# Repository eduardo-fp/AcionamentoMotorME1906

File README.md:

# 🚀 Arduino Full-Bridge Shield: Acionamento de Potência para Motor ME19006 (ME0909)

O objetivo principal é criar uma ponte completa (*Full-Bridge*) robusta e didática para realizar ensaios de eficiência e testes de técnicas avançadas de modulação chaveada no motor **ME19006 (ME0909)**, utilizado no barco da equipe de corrida **Zênite Solar (IFSC)**.

A arquitetura foi pensada em formato Shield para o ecossistema Arduino, facilitando a troca rápida de códigos de controle e aquisição de dados durante as bancadas de teste.

## 📋 Especificações do Sistema

O projeto foi dimensionado para operar nas condições reais de teste da equipe de barco solar, trabalhando com alta margem de segurança elétrica e térmica:

| **Parâmetro / Componente** | **Especificação** | **Descrição / Justificativa** |
| :--- | :--- | :--- |
| **Tensão de Barramento** | `60V DC` | Tensão nominal de alimentação do barramento de tração do barco da equipe **Zênite Solar (IFSC)**. |
| **Corrente Máxima** | `50A` | Corrente máxima de teste estipulada para validação das modulações do TCC. |
| **Motor Alvo** | `ME19006 (ME0909)` | Motor utilizado no barco da equipe Zenite Solar (IFSC). |
| **Gate Driver** | `MP1923` | Driver Half-Bridge de 100V. Fornece 7A/8A de pico. |
| **MOSFET de Potência** | `IXFN420N10T` | MOSFET utilizado no barco da equipe Zenite Solar(IFSC). |
| **Frequência de Chaveamento** | `6 kHz a 12 kHz` | Faixa de frequência de modulação otimizada para o motor e para minimizar perdas no driver. |

## 🛡️ Destaques de Projeto da PCB

Para garantir que a placa funcione de forma estável sob correntes de 50A e barramento de 60V, as seguintes proteções e metodologias foram implementadas no layout:

1. **Rede de Bootstrap Otimizada:** Dimensionada utilizando o pior caso de chaveamento (**6 kHz**). Capacitores cerâmicos SMD de **4.7 µF (50V X7R)** foram selecionados para compensar as correntes quiescentes do driver e a perda de capacitância por efeito de *DC Bias*.

2. **Filtros Snubber RC:** Integrados fisicamente rentes aos drenos e fontes dos MOSFETs IXFN420N10T para mitigar os picos de sobretensão causados pela indutância parasita das trilhas na comutação.

3. **Dimensionamento de Trilhas de Potência:** Áreas de cobre superdimensionadas e estanhadas para suportar a densidade de corrente de 50A sem elevação excessiva de temperatura (calculado via IPC-2152).

## 📂 Estrutura do Repositório

O repositório está organizado para facilitar a replicação, fabricação e auditoria do projeto:

```text
📦 AcionamentoMotorME1906
 ┣ 📂 Hardware
 ┃ ┣ 📜 Esquemático (Arquivos fontes e PDF)
 ┃ ┣ 📜 PCB Layout (Arquivos de design e Gerbers para fabricação)
 ┃ ┣ 📜 BOM_Custos.csv (Lista de Materials e Orçamento do Projeto)
 ┃ ┗ 📜 Modelos 3D (Arquivos STEP para integração mecânica do Shield)
 ┣ 📂 Docs
 ┃ ┣ 📜 Calculos (Bootstrap, Snubber e dimensionamento de trilhas)
 ┃ ┗ 📜 Datasheets (Documentações técnicas do MP1923 e IXFN420N10T)
 ┣ 📂 Software
 ┃ ┗ 📜 Codigos Arduino (Implementação das rotinas de controle e PWM)
 ┗ 📜 README.md

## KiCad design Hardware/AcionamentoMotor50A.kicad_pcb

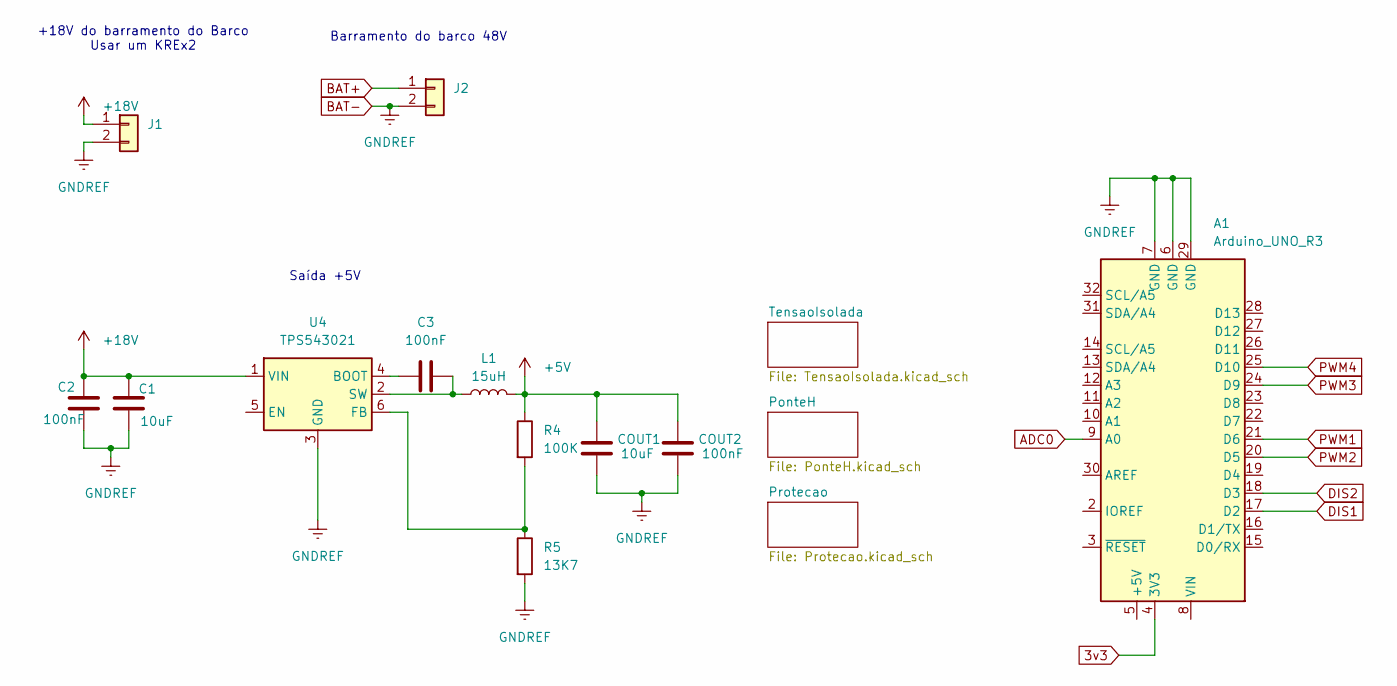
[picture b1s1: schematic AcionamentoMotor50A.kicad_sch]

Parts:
A1: Arduino_UNO_R3
C1: 10uF; C_0805_2012Metric_Pad1.18x1.45mm_HandSolder
C2, C3: 100nF; C_0805_2012Metric_Pad1.18x1.45mm_HandSolder
COUT1: 10uF; C_0805_2012Metric_Pad1.18x1.45mm_HandSolder
COUT2: 100nF; C_0805_2012Metric_Pad1.18x1.45mm_HandSolder
J1, J2: Conn_01x02; TerminalBlock_Phoenix_MKDS-1,5-2_1x02_P5.00mm_Horizontal
L1: 15uH; L_0805_2012Metric_Pad1.05x1.20mm_HandSolder
R4: 100K; R_0805_2012Metric_Pad1.20x1.40mm_HandSolder
R5: 13K7; R_0805_2012Metric_Pad1.20x1.40mm_HandSolder
U4: TPS543021; SOT-563

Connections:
3v3: A1.4 (3V3)
5V: COUT1.2, COUT2.2, L1.2, R4.1; also elsewhere on the board
+18V: C1.1, C2.1, J1.1, U4.1 (VIN); also elsewhere on the board
ADC0: A1.9 (A0); also elsewhere on the board
BAT+: J2.1; also elsewhere on the board
BAT-: A1.6 (GND), A1.7 (GND), A1.29 (GND), C1.2, C2.2, COUT1.1, COUT2.1, J1.2, J2.2, R5.2, U4.3 (GND); also elsewhere on the board
DIS1: A1.17 (D2); also elsewhere on the board
DIS2: A1.18 (D3); also elsewhere on the board
unnamed: C3.1, U4.4 (BOOT)
unnamed: R4.2, R5.1, U4.6 (FB)
unnamed: C3.2, L1.1, U4.2 (SW)
PWM1: A1.21 (D6); also elsewhere on the board
PWM2: A1.20 (D5); also elsewhere on the board
PWM3: A1.24 (D9); also elsewhere on the board
PWM4: A1.25 (D10); also elsewhere on the board

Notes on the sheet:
Saída +5V
Barramento do barco 48V
+18V do barramento do Barco Usar um KREx2

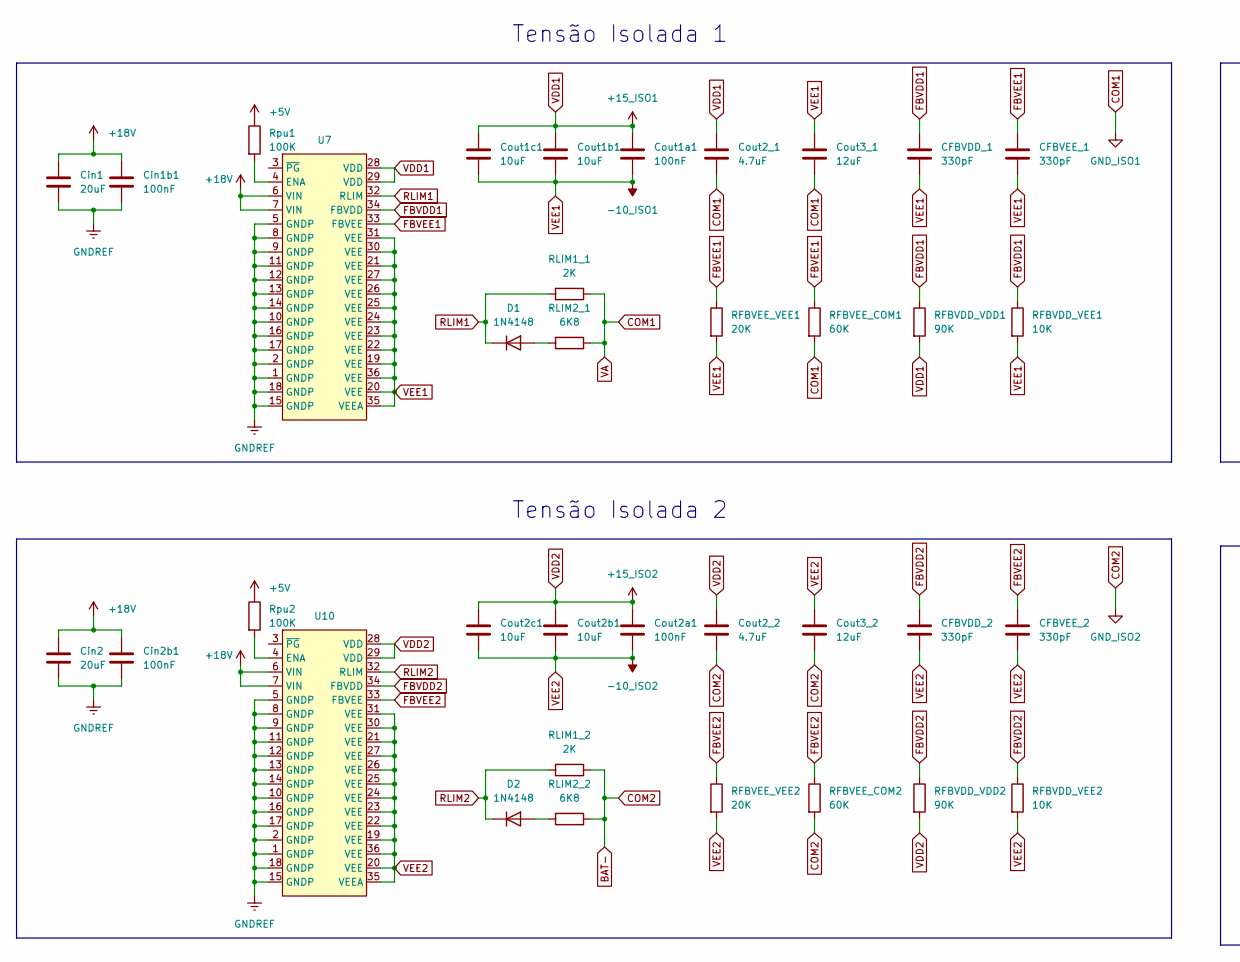
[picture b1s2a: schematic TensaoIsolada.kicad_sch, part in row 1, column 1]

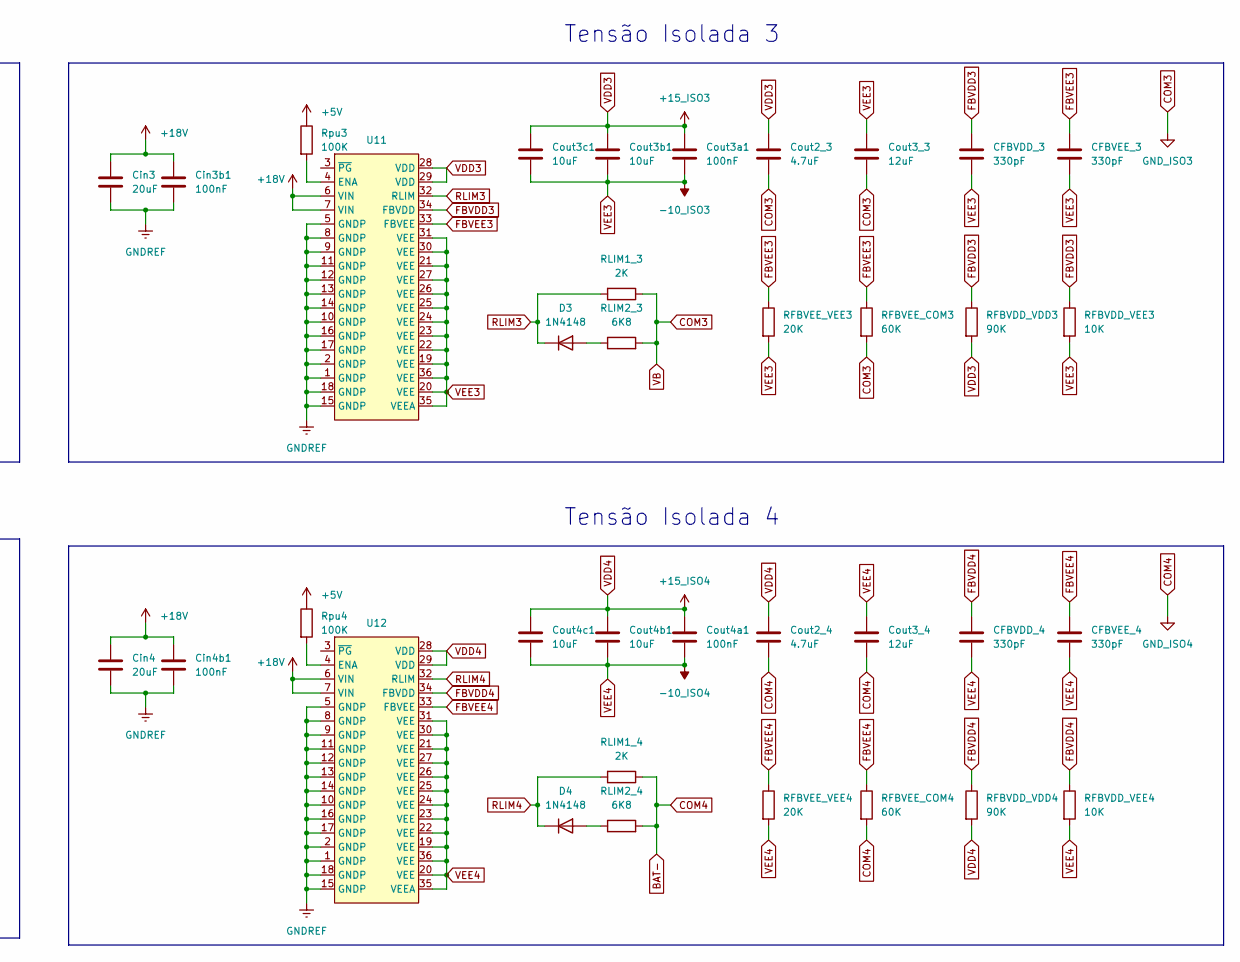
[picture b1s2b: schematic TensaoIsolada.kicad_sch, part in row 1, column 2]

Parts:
CFBVDD_1, CFBVDD_2, CFBVDD_3, CFBVDD_4: 330pF; C_0805_2012Metric_Pad1.18x1.45mm_HandSolder
CFBVEE_1, CFBVEE_2, CFBVEE_3, CFBVEE_4: 330pF; C_0805_2012Metric_Pad1.18x1.45mm_HandSolder
Cin1, Cin2, Cin3, Cin4: 20uF; C_0805_2012Metric_Pad1.18x1.45mm_HandSolder
Cin1b1, Cin2b1, Cin3b1, Cin4b1: 100nF; C_0805_2012Metric_Pad1.18x1.45mm_HandSolder
Cout1a1, Cout2a1, Cout3a1, Cout4a1: 100nF; C_0805_2012Metric_Pad1.18x1.45mm_HandSolder
Cout1b1, Cout1c1, Cout2b1, Cout2c1, Cout3b1, Cout3c1, Cout4b1, Cout4c1: 10uF; C_0805_2012Metric_Pad1.18x1.45mm_HandSolder
Cout2_1, Cout2_2, Cout2_3, Cout2_4: 4.7uF; C_0805_2012Metric_Pad1.18x1.45mm_HandSolder
Cout3_1, Cout3_2, Cout3_3, Cout3_4: 12uF; C_0805_2012Metric_Pad1.18x1.45mm_HandSolder
D1, D2, D3, D4: 1N4148; D_DO-35_SOD27_P7.62mm_Horizontal
RFBVDD_VDD1, RFBVDD_VDD2, RFBVDD_VDD3, RFBVDD_VDD4: 90K; R_0805_2012Metric_Pad1.20x1.40mm_HandSolder
RFBVDD_VEE1, RFBVDD_VEE2, RFBVDD_VEE3, RFBVDD_VEE4: 10K; R_0805_2012Metric_Pad1.20x1.40mm_HandSolder
RFBVEE_COM1, RFBVEE_COM2, RFBVEE_COM3, RFBVEE_COM4: 60K; R_0805_2012Metric_Pad1.20x1.40mm_HandSolder
RFBVEE_VEE1, RFBVEE_VEE2, RFBVEE_VEE3, RFBVEE_VEE4: 20K; R_0805_2012Metric_Pad1.20x1.40mm_HandSolder
RLIM1_1, RLIM1_2, RLIM1_3, RLIM1_4: 2K; R_0805_2012Metric_Pad1.20x1.40mm_HandSolder
RLIM2_1, RLIM2_2, RLIM2_3, RLIM2_4: 6K8; R_0805_2012Metric_Pad1.20x1.40mm_HandSolder
Rpu1, Rpu2, Rpu3, Rpu4: 100K; R_0805_2012Metric_Pad1.20x1.40mm_HandSolder
U7, U10, U11, U12: SSOP-36

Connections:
5V: Rpu1.1, Rpu2.1, Rpu3.1, Rpu4.1; also elsewhere on the board
+18V: Cin1.1, Cin1b1.1, Cin2.1, Cin2b1.1, Cin3.1, Cin3b1.1, Cin4.1, Cin4b1.1, U7.6 (VIN), U7.7 (VIN), U10.6 (VIN), U10.7 (VIN), U11.6 (VIN), U11.7 (VIN), U12.6 (VIN), U12.7 (VIN); also elsewhere on the board
BAT-: Cin1.2, Cin1b1.2, Cin2.2, Cin2b1.2, Cin3.2, Cin3b1.2, Cin4.2, Cin4b1.2, Cout2_2.2, Cout2_4.2, Cout3_2.2, Cout3_4.2, RFBVEE_COM2.2, RFBVEE_COM4.2, RLIM1_2.1, RLIM1_4.1, RLIM2_2.2, RLIM2_4.2, U7.1 (GNDP), U7.2 (GNDP), U7.5 (GNDP), U7.8 (GNDP), U7.9 (GNDP), U7.10 (GNDP), U7.11 (GNDP), U7.12 (GNDP), U7.13 (GNDP), U7.14 (GNDP), U7.15 (GNDP), U7.16 (GNDP), U7.17 (GNDP), U7.18 (GNDP), U10.1 (GNDP), U10.2 (GNDP), U10.5 (GNDP), U10.8 (GNDP), U10.9 (GNDP), U10.10 (GNDP), U10.11 (GNDP), U10.12 (GNDP), U10.13 (GNDP), U10.14 (GNDP), U10.15 (GNDP), U10.16 (GNDP), U10.17 (GNDP), U10.18 (GNDP), U11.1 (GNDP), U11.2 (GNDP), U11.5 (GNDP), U11.8 (GNDP), U11.9 (GNDP), U11.10 (GNDP), U11.11 (GNDP), U11.12 (GNDP), U11.13 (GNDP), U11.14 (GNDP), U11.15 (GNDP), U11.16 (GNDP), U11.17 (GNDP), U11.18 (GNDP), U12.1 (GNDP), U12.2 (GNDP), U12.5 (GNDP), U12.8 (GNDP), U12.9 (GNDP), U12.10 (GNDP), U12.11 (GNDP), U12.12 (GNDP), U12.13 (GNDP), U12.14 (GNDP), U12.15 (GNDP), U12.16 (GNDP), U12.17 (GNDP), U12.18 (GNDP); also elsewhere on the board
COM1: Cout2_1.2, Cout3_1.2, RFBVEE_COM1.2, RLIM1_1.1, RLIM2_1.2; also elsewhere on the board
COM3: Cout2_3.2, Cout3_3.2, RFBVEE_COM3.2, RLIM1_3.1, RLIM2_3.2; also elsewhere on the board
FBVDD1: CFBVDD_1.1, RFBVDD_VDD1.1, RFBVDD_VEE1.1, U7.34 (FBVDD)
FBVDD2: CFBVDD_2.1, RFBVDD_VDD2.1, RFBVDD_VEE2.1, U10.34 (FBVDD)
FBVDD3: CFBVDD_3.1, RFBVDD_VDD3.1, RFBVDD_VEE3.1, U11.34 (FBVDD)
FBVDD4: CFBVDD_4.1, RFBVDD_VDD4.1, RFBVDD_VEE4.1, U12.34 (FBVDD)
FBVEE1: CFBVEE_1.1, RFBVEE_COM1.1, RFBVEE_VEE1.1, U7.33 (FBVEE)
FBVEE2: CFBVEE_2.1, RFBVEE_COM2.1, RFBVEE_VEE2.1, U10.33 (FBVEE)
FBVEE3: CFBVEE_3.1, RFBVEE_COM3.1, RFBVEE_VEE3.1, U11.33 (FBVEE)
FBVEE4: CFBVEE_4.1, RFBVEE_COM4.1, RFBVEE_VEE4.1, U12.33 (FBVEE)
unnamed: D1.2 (A), RLIM2_1.1
unnamed: D2.2 (A), RLIM2_2.1
unnamed: D3.2 (A), RLIM2_3.1
unnamed: D4.2 (A), RLIM2_4.1
unnamed: Rpu1.2, U7.4 (ENA)
unnamed: Rpu2.2, U10.4 (ENA)
unnamed: Rpu3.2, U11.4 (ENA)
unnamed: Rpu4.2, U12.4 (ENA)
RLIM1: D1.1 (K), RLIM1_1.2, U7.32 (RLIM)
RLIM2: D2.1 (K), RLIM1_2.2, U10.32 (RLIM)
RLIM3: D3.1 (K), RLIM1_3.2, U11.32 (RLIM)
RLIM4: D4.1 (K), RLIM1_4.2, U12.32 (RLIM)
VDD1: Cout1a1.1, Cout1b1.1, Cout1c1.1, Cout2_1.1, RFBVDD_VDD1.2, U7.28 (VDD), U7.29 (VDD); also elsewhere on the board
VDD2: Cout2_2.1, Cout2a1.1, Cout2b1.1, Cout2c1.1, RFBVDD_VDD2.2, U10.28 (VDD), U10.29 (VDD); also elsewhere on the board
VDD3: Cout2_3.1, Cout3a1.1, Cout3b1.1, Cout3c1.1, RFBVDD_VDD3.2, U11.28 (VDD), U11.29 (VDD); also elsewhere on the board
VDD4: Cout2_4.1, Cout4a1.1, Cout4b1.1, Cout4c1.1, RFBVDD_VDD4.2, U12.28 (VDD), U12.29 (VDD); also elsewhere on the board
VEE1: CFBVDD_1.2, CFBVEE_1.2, Cout1a1.2, Cout1b1.2, Cout1c1.2, Cout3_1.1, RFBVDD_VEE1.2, RFBVEE_VEE1.2, U7.19 (VEE), U7.20 (VEE), U7.21 (VEE), U7.22 (VEE), U7.23 (VEE), U7.24 (VEE), U7.25 (VEE), U7.26 (VEE), U7.27 (VEE), U7.30 (VEE), U7.31 (VEE), U7.35 (VEEA), U7.36 (VEE); also elsewhere on the board
VEE2: CFBVDD_2.2, CFBVEE_2.2, Cout2a1.2, Cout2b1.2, Cout2c1.2, Cout3_2.1, RFBVDD_VEE2.2, RFBVEE_VEE2.2, U10.19 (VEE), U10.20 (VEE), U10.21 (VEE), U10.22 (VEE), U10.23 (VEE), U10.24 (VEE), U10.25 (VEE), U10.26 (VEE), U10.27 (VEE), U10.30 (VEE), U10.31 (VEE), U10.35 (VEEA), U10.36 (VEE); also elsewhere on the board
VEE3: CFBVDD_3.2, CFBVEE_3.2, Cout3_3.1, Cout3a1.2, Cout3b1.2, Cout3c1.2, RFBVDD_VEE3.2, RFBVEE_VEE3.2, U11.19 (VEE), U11.20 (VEE), U11.21 (VEE), U11.22 (VEE), U11.23 (VEE), U11.24 (VEE), U11.25 (VEE), U11.26 (VEE), U11.27 (VEE), U11.30 (VEE), U11.31 (VEE), U11.35 (VEEA), U11.36 (VEE); also elsewhere on the board
VEE4: CFBVDD_4.2, CFBVEE_4.2, Cout3_4.1, Cout4a1.2, Cout4b1.2, Cout4c1.2, RFBVDD_VEE4.2, RFBVEE_VEE4.2, U12.19 (VEE), U12.20 (VEE), U12.21 (VEE), U12.22 (VEE), U12.23 (VEE), U12.24 (VEE), U12.25 (VEE), U12.26 (VEE), U12.27 (VEE), U12.30 (VEE), U12.31 (VEE), U12.35 (VEEA), U12.36 (VEE); also elsewhere on the board

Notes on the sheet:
Tensão Isolada 4
Tensão Isolada 1
Tensão Isolada 2
Tensão Isolada 3

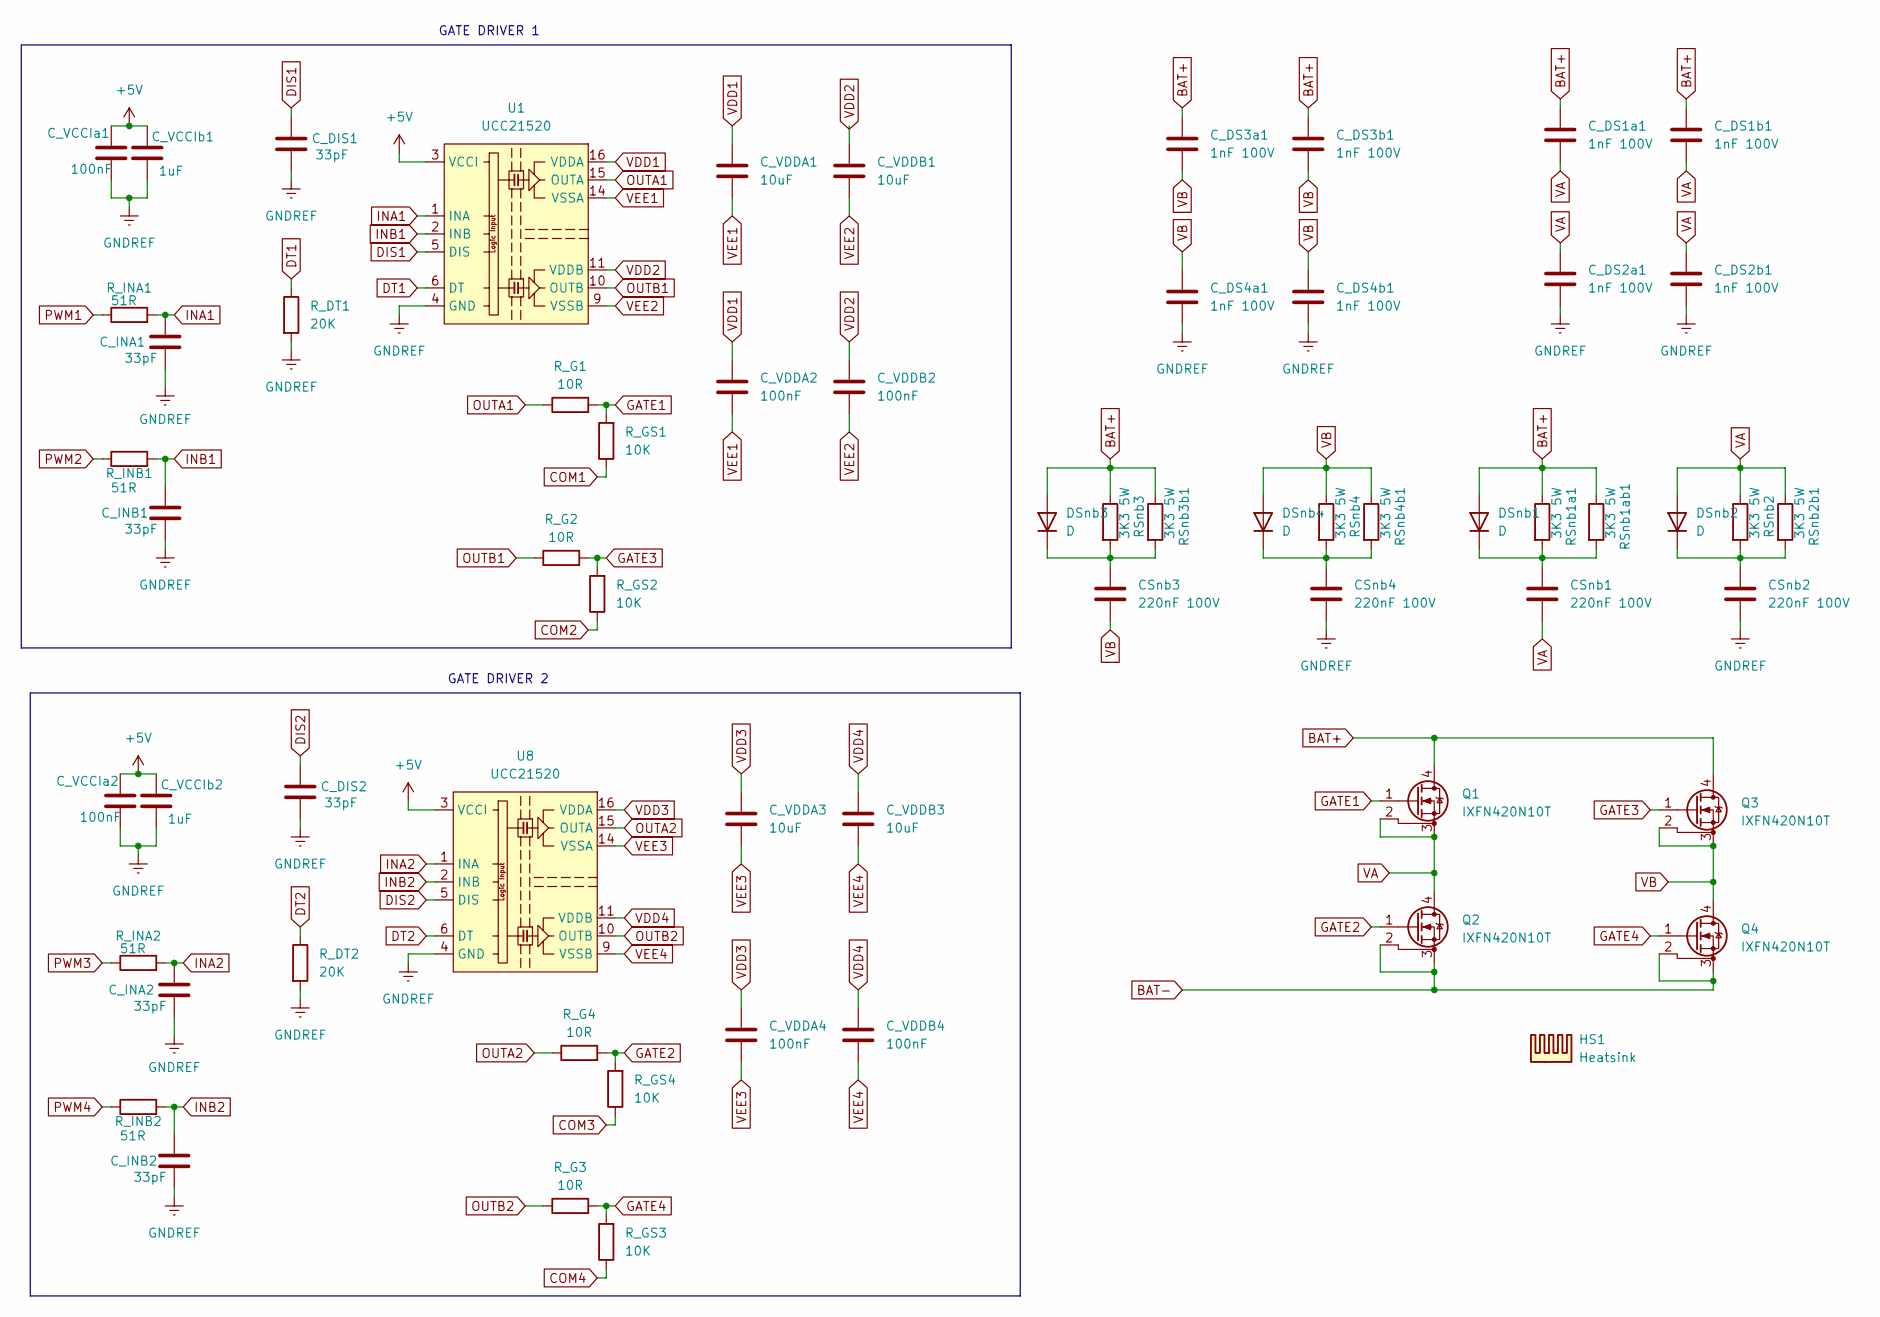
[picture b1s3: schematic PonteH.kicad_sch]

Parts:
CSnb1, CSnb2, CSnb3, CSnb4: 220nF 100V; C_Axial_L5.1mm_D3.1mm_P10.00mm_Horizontal
C_DIS1, C_DIS2: 33pF; C_0805_2012Metric_Pad1.18x1.45mm_HandSolder
C_DS1a1, C_DS1b1, C_DS2a1, C_DS2b1, C_DS3a1, C_DS3b1, C_DS4a1, C_DS4b1: 1nF 100V; C_0805_2012Metric_Pad1.18x1.45mm_HandSolder
C_INA1, C_INA2: 33pF; C_0805_2012Metric_Pad1.18x1.45mm_HandSolder
C_INB1, C_INB2: 33pF; C_0805_2012Metric_Pad1.18x1.45mm_HandSolder
C_VCCI​a1, C_VCCI​a2: 100nF; C_0805_2012Metric_Pad1.18x1.45mm_HandSolder
C_VCCI​b1, C_VCCI​b2: 1uF; C_0805_2012Metric_Pad1.18x1.45mm_HandSolder
C_VDDA1, C_VDDA3: 10uF; C_0805_2012Metric_Pad1.18x1.45mm_HandSolder
C_VDDA2, C_VDDA4: 100nF; C_0805_2012Metric_Pad1.18x1.45mm_HandSolder
C_VDDB1, C_VDDB3: 10uF; C_0805_2012Metric_Pad1.18x1.45mm_HandSolder
C_VDDB2, C_VDDB4: 100nF; C_0805_2012Metric_Pad1.18x1.45mm_HandSolder
DSnb1, DSnb2, DSnb3, DSnb4: D; D_SMA_Handsoldering
HS1: Heatsink; Heatsink_120mmx100mm_H70mm
Q1, Q2, Q3, Q4: IXFN420N10T; SOT-227
RSnb1a1, RSnb1ab1, RSnb2, RSnb2b1, RSnb3, RSnb3b1, RSnb4, RSnb4b1: 3K3 5W; R_Axial_Power_L25.0mm_W9.0mm_P27.94mm
R_DT1, R_DT2: 20K; R_0805_2012Metric_Pad1.20x1.40mm_HandSolder
R_G1, R_G2, R_G3, R_G4: 10R; R_0805_2012Metric_Pad1.20x1.40mm_HandSolder
R_GS1, R_GS2, R_GS3, R_GS4: 10K; R_0805_2012Metric_Pad1.20x1.40mm_HandSolder
R_INA1, R_INA2: 51R; R_0805_2012Metric_Pad1.20x1.40mm_HandSolder
R_INB1, R_INB2: 51R; R_0805_2012Metric_Pad1.20x1.40mm_HandSolder
U1, U8: UCC21520; SOIC-16W_7.5x10.3mm_P1.27mm

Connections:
5V: C_VCCI​a1.1, C_VCCI​a2.1, C_VCCI​b1.1, C_VCCI​b2.1, U1.3 (VCCI), U1.8 (VCCI), U8.3 (VCCI), U8.8 (VCCI); also elsewhere on the board
BAT+: C_DS1a1.1, C_DS1b1.1, C_DS3a1.1, C_DS3b1.1, DSnb1.2 (A), DSnb3.2 (A), Q1.4 (D), Q3.4 (D), RSnb1a1.1, RSnb1ab1.1, RSnb3.1, RSnb3b1.1; also elsewhere on the board
BAT-: CSnb2.2, CSnb4.2, C_DIS1.2, C_DIS2.2, C_DS2a1.2, C_DS2b1.2, C_DS4a1.2, C_DS4b1.2, C_INA1.2, C_INA2.2, C_INB1.2, C_INB2.2, C_VCCI​a1.2, C_VCCI​a2.2, C_VCCI​b1.2, C_VCCI​b2.2, Q2.2 (DS), Q2.3 (S), Q4.2 (DS), Q4.3 (S), R_DT1.2, R_DT2.2, R_GS2.1, R_GS3.1, U1.4 (GND), U8.4 (GND); also elsewhere on the board
COM1: CSnb1.2, C_DS1a1.2, C_DS1b1.2, C_DS2a1.1, C_DS2b1.1, DSnb2.2 (A), Q1.2 (DS), Q1.3 (S), Q2.4 (D), RSnb2.1, RSnb2b1.1, R_GS1.1; also elsewhere on the board
COM3: CSnb3.2, C_DS3a1.2, C_DS3b1.2, C_DS4a1.1, C_DS4b1.1, DSnb4.2 (A), Q3.2 (DS), Q3.3 (S), Q4.4 (D), RSnb4.1, RSnb4b1.1, R_GS4.1; also elsewhere on the board
DIS1: C_DIS1.1, U1.5 (DIS); also elsewhere on the board
DIS2: C_DIS2.1, U8.5 (DIS); also elsewhere on the board
DT1: R_DT1.1, U1.6 (DT)
DT2: R_DT2.1, U8.6 (DT)
GATE1: Q1.1 (G), R_G1.2, R_GS1.2
GATE2: Q2.1 (G), R_G4.2, R_GS4.2
GATE3: Q3.1 (G), R_G2.2, R_GS2.2
GATE4: Q4.1 (G), R_G3.2, R_GS3.2
INA1: C_INA1.1, R_INA1.2, U1.1 (INA)
INA2: C_INA2.1, R_INA2.2, U8.1 (INA)
INB1: C_INB1.1, R_INB1.2, U1.2 (INB)
INB2: C_INB2.1, R_INB2.2, U8.2 (INB)
unnamed: CSnb1.1, DSnb1.1 (K), RSnb1a1.2, RSnb1ab1.2
unnamed: CSnb2.1, DSnb2.1 (K), RSnb2.2, RSnb2b1.2
unnamed: CSnb3.1, DSnb3.1 (K), RSnb3.2, RSnb3b1.2
unnamed: CSnb4.1, DSnb4.1 (K), RSnb4.2, RSnb4b1.2
OUTA1: R_G1.1, U1.15 (OUTA)
OUTA2: R_G4.1, U8.15 (OUTA)
OUTB1: R_G2.1, U1.10 (OUTB)
OUTB2: R_G3.1, U8.10 (OUTB)
PWM1: R_INA1.1; also elsewhere on the board
PWM2: R_INB1.1; also elsewhere on the board
PWM3: R_INA2.1; also elsewhere on the board
PWM4: R_INB2.1; also elsewhere on the board
VDD1: C_VDDA1.1, C_VDDA2.1, U1.16 (VDDA); also elsewhere on the board
VDD2: C_VDDB1.1, C_VDDB2.1, U1.11 (VDDB); also elsewhere on the board
VDD3: C_VDDA3.1, C_VDDA4.1, U8.16 (VDDA); also elsewhere on the board
VDD4: C_VDDB3.1, C_VDDB4.1, U8.11 (VDDB); also elsewhere on the board
VEE1: C_VDDA1.2, C_VDDA2.2, U1.14 (VSSA); also elsewhere on the board
VEE2: C_VDDB1.2, C_VDDB2.2, U1.9 (VSSB); also elsewhere on the board
VEE3: C_VDDA3.2, C_VDDA4.2, U8.14 (VSSA); also elsewhere on the board
VEE4: C_VDDB3.2, C_VDDB4.2, U8.9 (VSSB); also elsewhere on the board

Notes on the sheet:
GATE DRIVER 1
GATE DRIVER 2

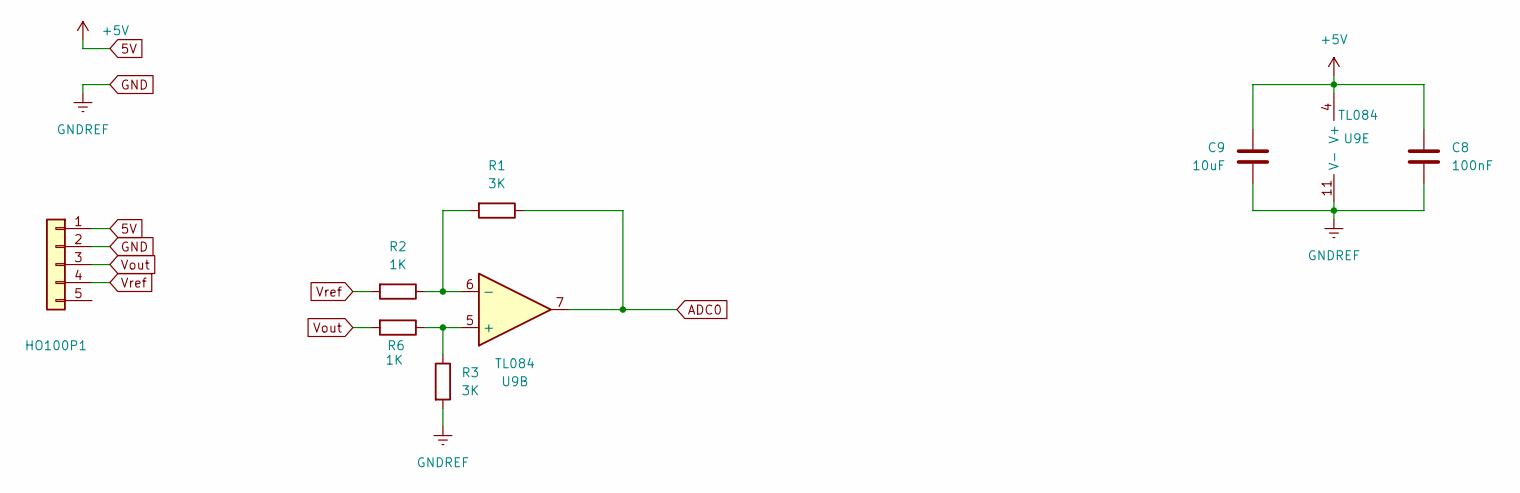
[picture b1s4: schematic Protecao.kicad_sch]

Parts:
C8: 100nF; C_0805_2012Metric_Pad1.18x1.45mm_HandSolder
C9: 10uF; C_0805_2012Metric_Pad1.18x1.45mm_HandSolder
HO100P1: Conn_01x05; Molex_KK-254_AE-6410-05A_1x05_P2.54mm_Vertical
R1, R3: 3K; R_0805_2012Metric_Pad1.20x1.40mm_HandSolder
R2, R6: 1K; R_0805_2012Metric_Pad1.20x1.40mm_HandSolder
U9: TL084; SOIC-14_3.9x8.7mm_P1.27mm

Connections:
5V: C8.1, C9.1, HO100P1.1, U9.4 (V+); also elsewhere on the board
ADC0: R1.1, U9.7; also elsewhere on the board
BAT-: C8.2, C9.2, HO100P1.2, R3.2, U9.11 (V-); also elsewhere on the board
unnamed: R3.1, R6.1, U9.5 (+)
unnamed: R1.2, R2.1, U9.6 (-)
Vout: HO100P1.3, R6.2
Vref: HO100P1.4, R2.2

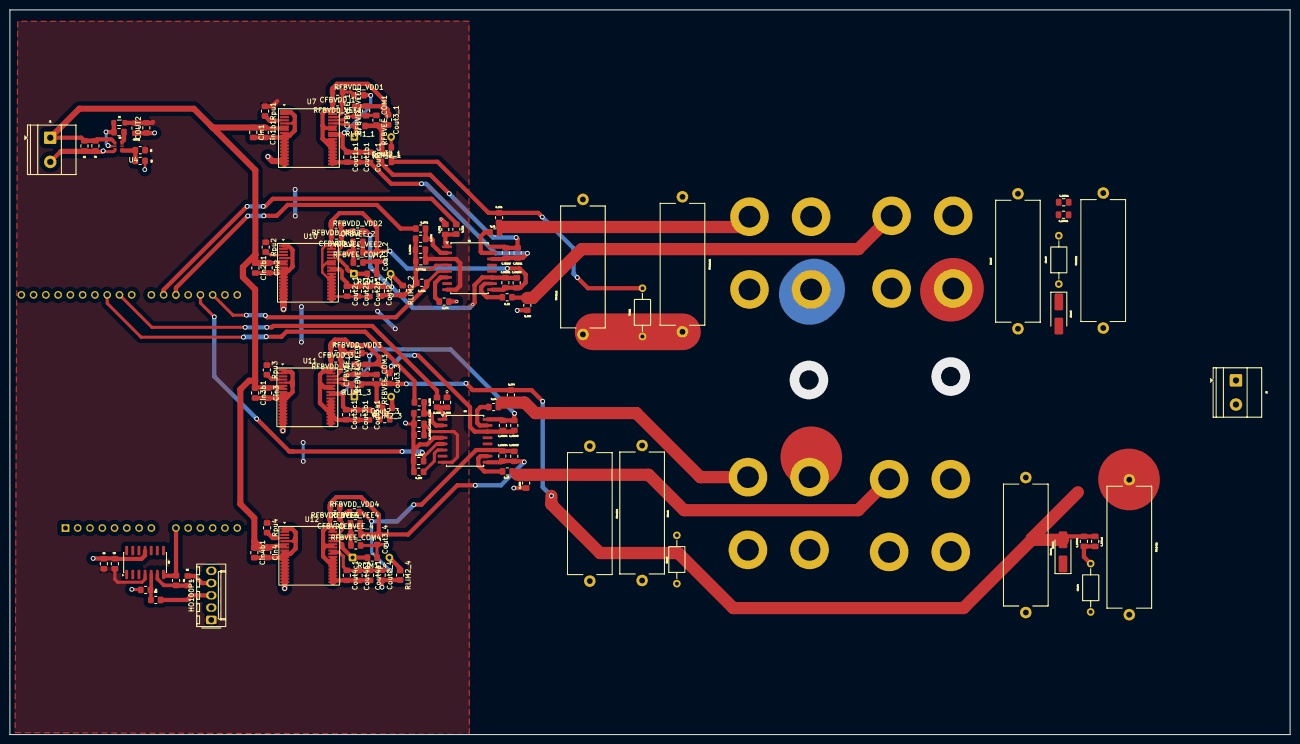
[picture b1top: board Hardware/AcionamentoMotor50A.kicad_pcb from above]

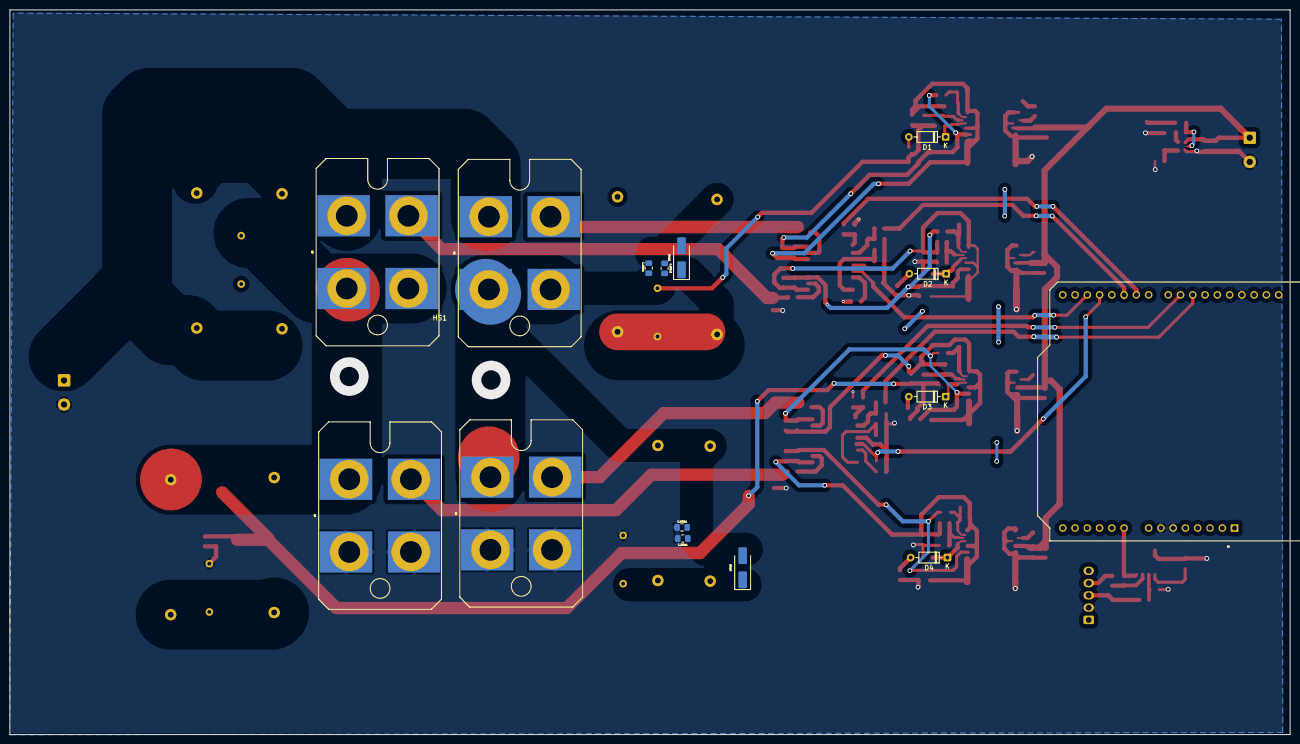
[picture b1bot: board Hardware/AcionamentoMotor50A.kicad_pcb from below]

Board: 2 copper layers, 265.0 x 150.0 mm, 155 parts (16 on the bottom side), 66 nets.

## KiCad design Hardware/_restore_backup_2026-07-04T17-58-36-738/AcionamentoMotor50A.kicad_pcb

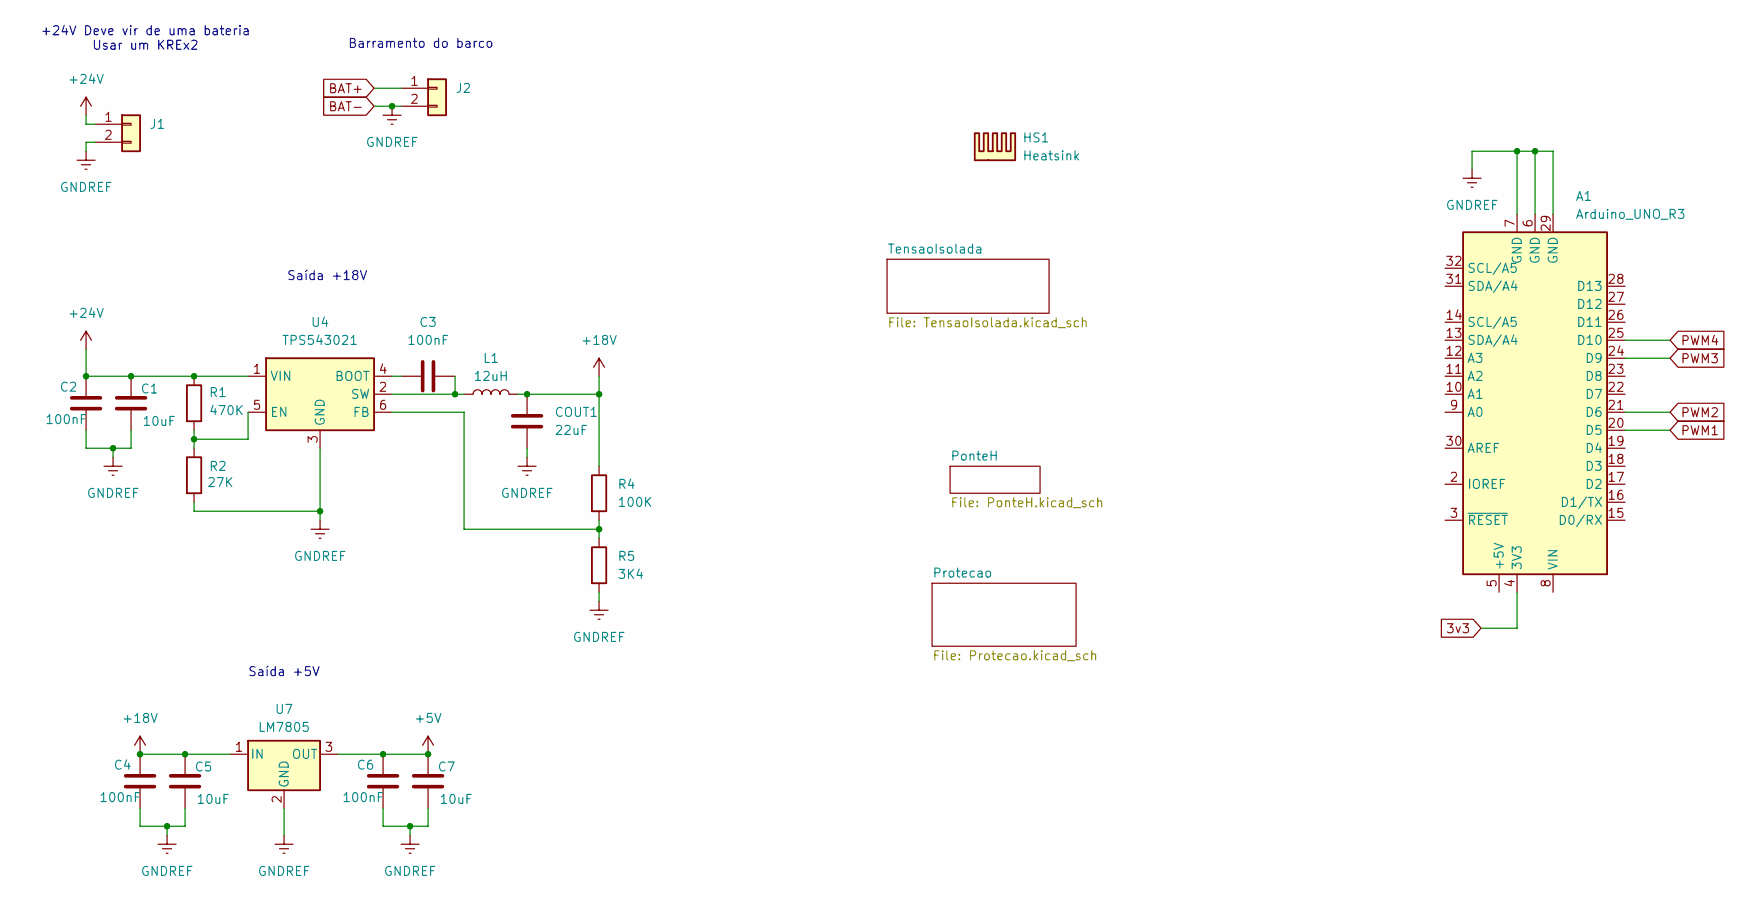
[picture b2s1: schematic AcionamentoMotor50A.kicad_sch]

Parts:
A1: Arduino_UNO_R3
C1, C5, C7: 10uF; C_0805_2012Metric_Pad1.18x1.45mm_HandSolder
C2, C3, C4, C6: 100nF; C_0805_2012Metric_Pad1.18x1.45mm_HandSolder
COUT1: 22uF; C_0805_2012Metric_Pad1.18x1.45mm_HandSolder
HS1: Heatsink; Heatsink_120mmx100mm_H70mm
J1, J2: Conn_01x02; TerminalBlock_Phoenix_MKDS-1,5-2_1x02_P5.00mm_Horizontal
L1: 12uH; L_0805_2012Metric_Pad1.05x1.20mm_HandSolder
R1: 470K; R_0805_2012Metric_Pad1.20x1.40mm_HandSolder
R2: 27K; R_0805_2012Metric_Pad1.20x1.40mm_HandSolder
R4: 100K; R_0805_2012Metric_Pad1.20x1.40mm_HandSolder
R5: 3K4; R_0805_2012Metric_Pad1.20x1.40mm_HandSolder
U4: TPS543021; SOT-23-6_Handsoldering
U7: LM7805; TO-220-3_Vertical

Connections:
3v3: A1.4 (3V3); also elsewhere on the board
+5V: C6.1, C7.1, U7.3 (OUT); also elsewhere on the board
+18V: C4.1, C5.1, COUT1.2, L1.2, R4.1, U7.1 (IN); also elsewhere on the board
+24V: C1.1, C2.1, J1.1, R1.1, U4.1 (VIN)
BAT+: J2.1; also elsewhere on the board
BAT-: A1.6 (GND), A1.7 (GND), A1.29 (GND), C1.2, C2.2, C4.2, C5.2, C6.2, C7.2, COUT1.1, J1.2, J2.2, R2.2, R5.2, U4.3 (GND), U7.2 (GND); also elsewhere on the board
unnamed: C3.1, U4.4 (BOOT)
unnamed: R1.2, R2.1, U4.5 (EN)
unnamed: R4.2, R5.1, U4.6 (FB)
unnamed: C3.2, L1.1, U4.2 (SW)
PWM1: A1.20 (D5); also elsewhere on the board
PWM2: A1.21 (D6); also elsewhere on the board
PWM3: A1.24 (D9); also elsewhere on the board
PWM4: A1.25 (D10); also elsewhere on the board

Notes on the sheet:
Saída +18V
Barramento do barco
Saída +5V
+24V Deve vir de uma bateria Usar um KREx2
